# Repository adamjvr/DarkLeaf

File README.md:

# DarkLeaf
Adafruit Feather style board for the STM32WB5MMGH6TR 2G RF Module

Quick Specs:
- STM32WB5MMGH6TR 2G RF Module
- Adafruit Feather pinout and formfactor
- ARM Cortex M Debug Port
- USB C Connector For DFU Flashing (USB 2.0 interface)
- LiPO powered w/ onboard 3.3V LDO Regulator
- Can be powered directly by 3.3V when breadboarded

KiCAD 2D PCB Render 

3D KiCAD PCB Renders 

Prototype made by OSHPark.com 

Released Under CERN Open Hardware License Version 2

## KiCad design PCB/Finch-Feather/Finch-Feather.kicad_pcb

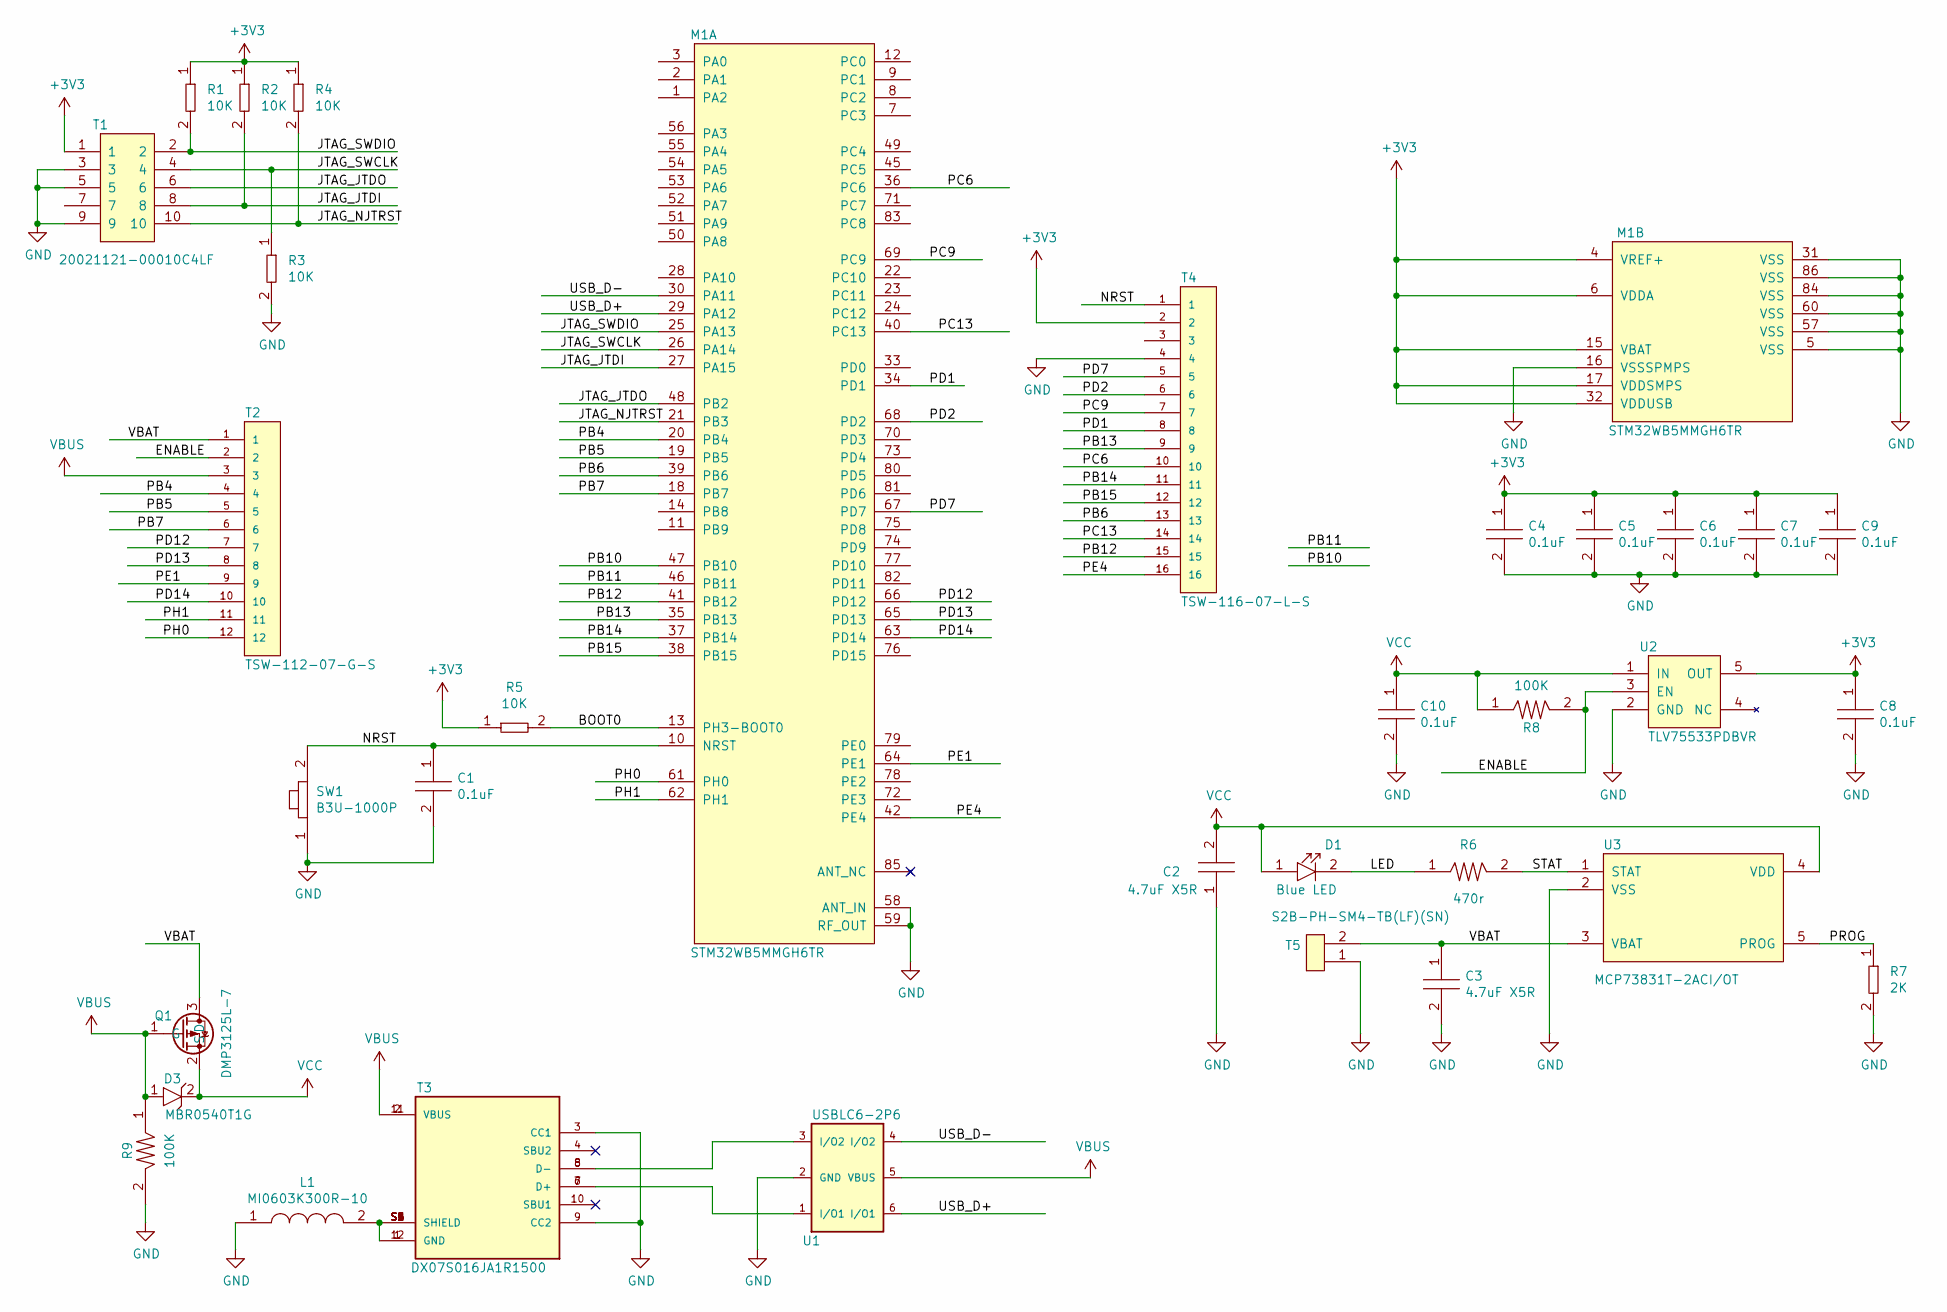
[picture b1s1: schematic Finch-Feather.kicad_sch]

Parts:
C1, C4, C5, C6, C7, C8, C9, C10: C0402C104K9PACTU; R0402; Tolerance 10%; Voltage 6.3V; MFR# C0402C104K9PACTU
C2, C3: C0603C475K9PACTU; C0603; Tolerance 10%; Voltage 6.3V; MFR# C0603C475K9PACTU
D1: LTST-C194TBKT; LED0603; Tolerance *; Voltage 3.3V; MFR# LTST-C194TBKT
D3: MBR0540T1G; D_SOD-123; Tolerance *; Voltage 40V; MFR# MBR0540T1G
L1: MI0603K300R-10; Tolerance *; Voltage *; MFR# MI0603K300R-10
M1: STM32WB5MMGH6TR; Tolerance *; Voltage 1.71-3.6V; MFR# STM32WB5MMGH6TR
Q1: DMP3125L-7; SOT-23; Tolerance *; Voltage 20V; MFR# DMP3125L-7
R1, R2, R3, R4, R5: RC0402FR-0710KL; R0402; Tolerance 1%; Voltage *; MFR# RC0402FR-0710KL
R6: RC0603FR-07470RL; R0603; Tolerance 1%; Voltage *; MFR# RC0603FR-07470RL
R7: RC0402FR-072KL; R0402; Tolerance 1%; Voltage *; MFR# RC0402FR-072KL
R8, R9: RC0603FR-07100KL; R0603; Tolerance 1%; Voltage *; MFR# RC0603FR-07100KL
SW1: B3U-1000P; Tolerance *; Voltage *; MFR# B3U-1000P
T1: 20021121-00010C4LF; Tolerance *; Voltage *; MFR# 20021121-00010C4LF
T2: TSW-112-07-G-S; SAMTEC-TSW-112-07-X-S; Tolerance *; Voltage *; MFR# TSW-112-07-G-S
T3: DX07S016JA1R1500; JAE_DX07S016JA1R1500; Tolerance *; Voltage 20V; MFR# DX07S016JA1R1500
T4: TSW-116-07-L-S; SAMTEC-TSW-116-07-X-S; Tolerance *; Voltage *; MFR# TSW-116-07-L-S
T5: S2B-PH-SM4-TB(LF)(SN); B2B-PH-SM4-TB(LF)(SN); Tolerance *; Voltage 94V; MFR# S2B-PH-SM4-TB(LF)(SN)
U1: USBLC6-2P6; SOT50P160X60-6N; Tolerance *; Voltage 17V Clamping; MFR# USBLC6-2P6
U2: TLV75533PDBVR; Tolerance *; Voltage 3.3V 500MA; MFR# TLV75533PDBVR
U3: MCP73831T-2ACI_OT; SOT-23-5; Tolerance *; Voltage *; MFR# MCP73831T-2ACI/OT

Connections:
+3V3: C4.1, C5.1, C6.1, C7.1, C8.1, C9.1, M1.4 (VREF+), M1.6 (VDDA), M1.15 (VBAT), M1.17 (VDDSMPS), M1.32 (VDDUSB), R1.1, R2.1, R4.1, R5.1, T1.1, T4.2, U2.5 (OUT)
/BOOT0: M1.13 (PH3-BOOT0), R5.2
/ENABLE: R8.2, T2.2, U2.3 (EN)
/JTAG_JTDI: M1.27 (PA15), R2.2, T1.8
/JTAG_JTDO: M1.48 (PB2), T1.6
/JTAG_NJTRST: M1.21 (PB3), R4.2, T1.10
/JTAG_SWCLK: M1.26 (PA14), R3.1, T1.4
/JTAG_SWDIO: M1.25 (PA13), R1.2, T1.2
/LED: D1.2, R6.1
/NRST: C1.1, M1.10 (NRST), SW1.2, T4.1
/PB4: M1.20 (PB4), T2.4
/PB5: M1.19 (PB5), T2.5
/PB6: M1.39 (PB6), T4.13
/PB7: M1.18 (PB7), T2.6
/PB10: M1.47 (PB10)
/PB11: M1.46 (PB11)
/PB12: M1.41 (PB12), T4.15
/PB13: M1.35 (PB13), T4.9
/PB14: M1.37 (PB14), T4.11
/PB15: M1.38 (PB15), T4.12
/PC6: M1.36 (PC6), T4.10
/PC9: M1.69 (PC9), T4.7
/PC13: M1.40 (PC13), T4.14
/PD1: M1.34 (PD1), T4.8
/PD2: M1.68 (PD2), T4.6
/PD7: M1.67 (PD7), T4.5
/PD12: M1.66 (PD12), T2.7
/PD13: M1.65 (PD13), T2.8
/PD14: M1.63 (PD14), T2.10
/PE1: M1.64 (PE1), T2.9
/PE4: M1.42 (PE4), T4.16
/PH0: M1.61 (PH0), T2.12
/PH1: M1.62 (PH1), T2.11
/PROG: R7.1, U3.5 (PROG)
/STAT: R6.2, U3.1 (STAT)
/USB_D+: M1.29 (PA12), U1.6 (I/O1)
/USB_D-: M1.30 (PA11), U1.4 (I/O2)
/VBAT: C3.1, Q1.3 (D), T2.1, T5.2, U3.3 (VBAT)
GND: C1.2, C2.1, C3.2, C4.2, C5.2, C6.2, C7.2, C8.2, C9.2, C10.2, L1.1, M1.5 (VSS), M1.16 (VSSSPMPS), M1.31 (VSS), M1.57 (VSS), M1.58 (ANT_IN), M1.59 (RF_OUT), M1.60 (VSS), M1.84 (VSS), M1.86 (VSS), R3.2, R7.2, R9.2, SW1.1, T1.3, T1.5, T1.9, T3.3 (CC1), T3.9 (CC2), T4.4, T5.1, U1.2 (GND), U2.2 (GND), U3.2 (VSS)
unnamed: L1.2, T3.1 (GND), T3.12 (GND), T3.S1 (SHIELD), T3.S2 (SHIELD), T3.S3 (SHIELD), T3.S4 (SHIELD), T3.S5 (SHIELD), T3.S6 (SHIELD)
unnamed: T3.5 (D-), T3.8 (D-), U1.3 (I/O2)
unnamed: T3.6 (D+), T3.7 (D+), U1.1 (I/O1)
VBUS: D3.1, Q1.1 (G), R9.1, T2.3, T3.2 (VBUS), T3.11 (VBUS), U1.5 (VBUS)
VCC: C2.2, C10.1, D1.1, D3.2, Q1.2 (S), R8.1, U2.1 (IN), U3.4 (VDD)

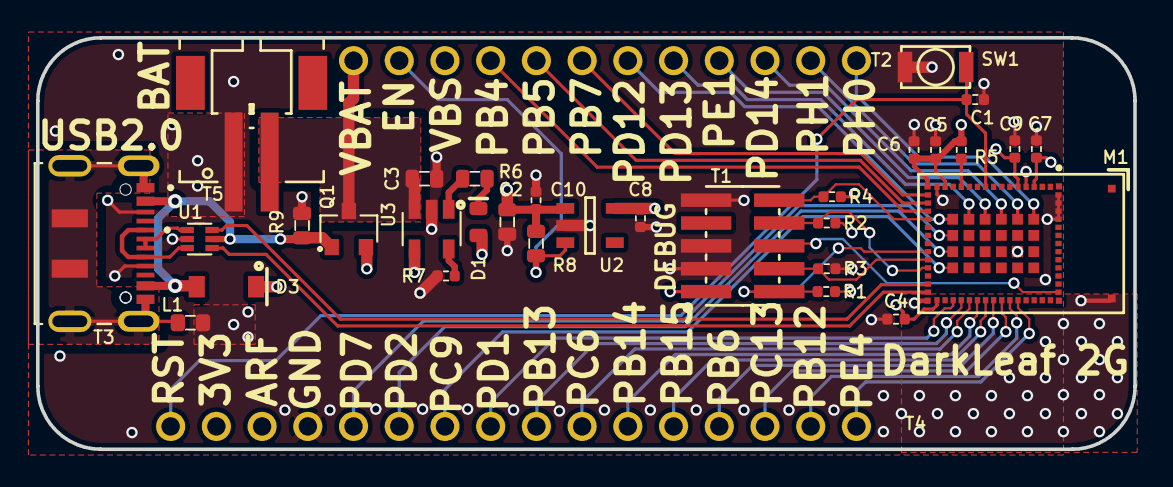
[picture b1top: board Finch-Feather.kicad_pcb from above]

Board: 4 copper layers, 61.0 x 22.9 mm, 33 parts (0 on the bottom side), 42 nets.

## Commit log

2021-02-14 Schematic
    First pass on schematic, still needs a few things before annotation
2021-02-14 PCB
    PCB started, next step figuring out which pins on module to use
2021-02-15 PCB Near Finished
    Head signals wired to pins on module, power supply section and USB connector are next
2021-02-19 PCB Progress
    More progress on PCB design, made some tweaks and changes, implemented enable circuit.
2021-02-21 PCB pass COmplete
    First true pass of PCB fully complete, with new power switching circuit and regulator enable. Smaller packages selected for pretty much every IC previously used.
2021-02-22 Heavy PCB Rework
    Reworked the Portion of the PCB around the ST RF module, signals re-chosen for 3 GPIOs to make the grounding conform more to the reference design recommendations.
2021-03-08 PCB changes
    Adjusted pours, next need to perfrom DRC, syncing for work
2021-04-07 Prefab changes
    minor adjustments, removal of screw holes, and additional via stitching
2023-08-14 Update README.md
    name change
2024-03-07 KiCAD Project Upadated and Images added
    Updated the KiCAD Project to the newest version, restored paths for 3D files for board components. Added 3D rendered images of the board.
2024-03-07 Update README.md
    Added quick specs and license info to the readme
2024-03-07 License
    Added markdown file for CERN Open Hardware License Version 2
2024-03-08 Image Test
    Testing if image renders in markdown, my Sublime Text package is broken so using git
2024-03-08 More Images Added to Readme
    Images added to readme !
2024-03-08 Read me updates
    Added more images and description to the readme
2025-03-11 Project Update
    Updated project to new version
